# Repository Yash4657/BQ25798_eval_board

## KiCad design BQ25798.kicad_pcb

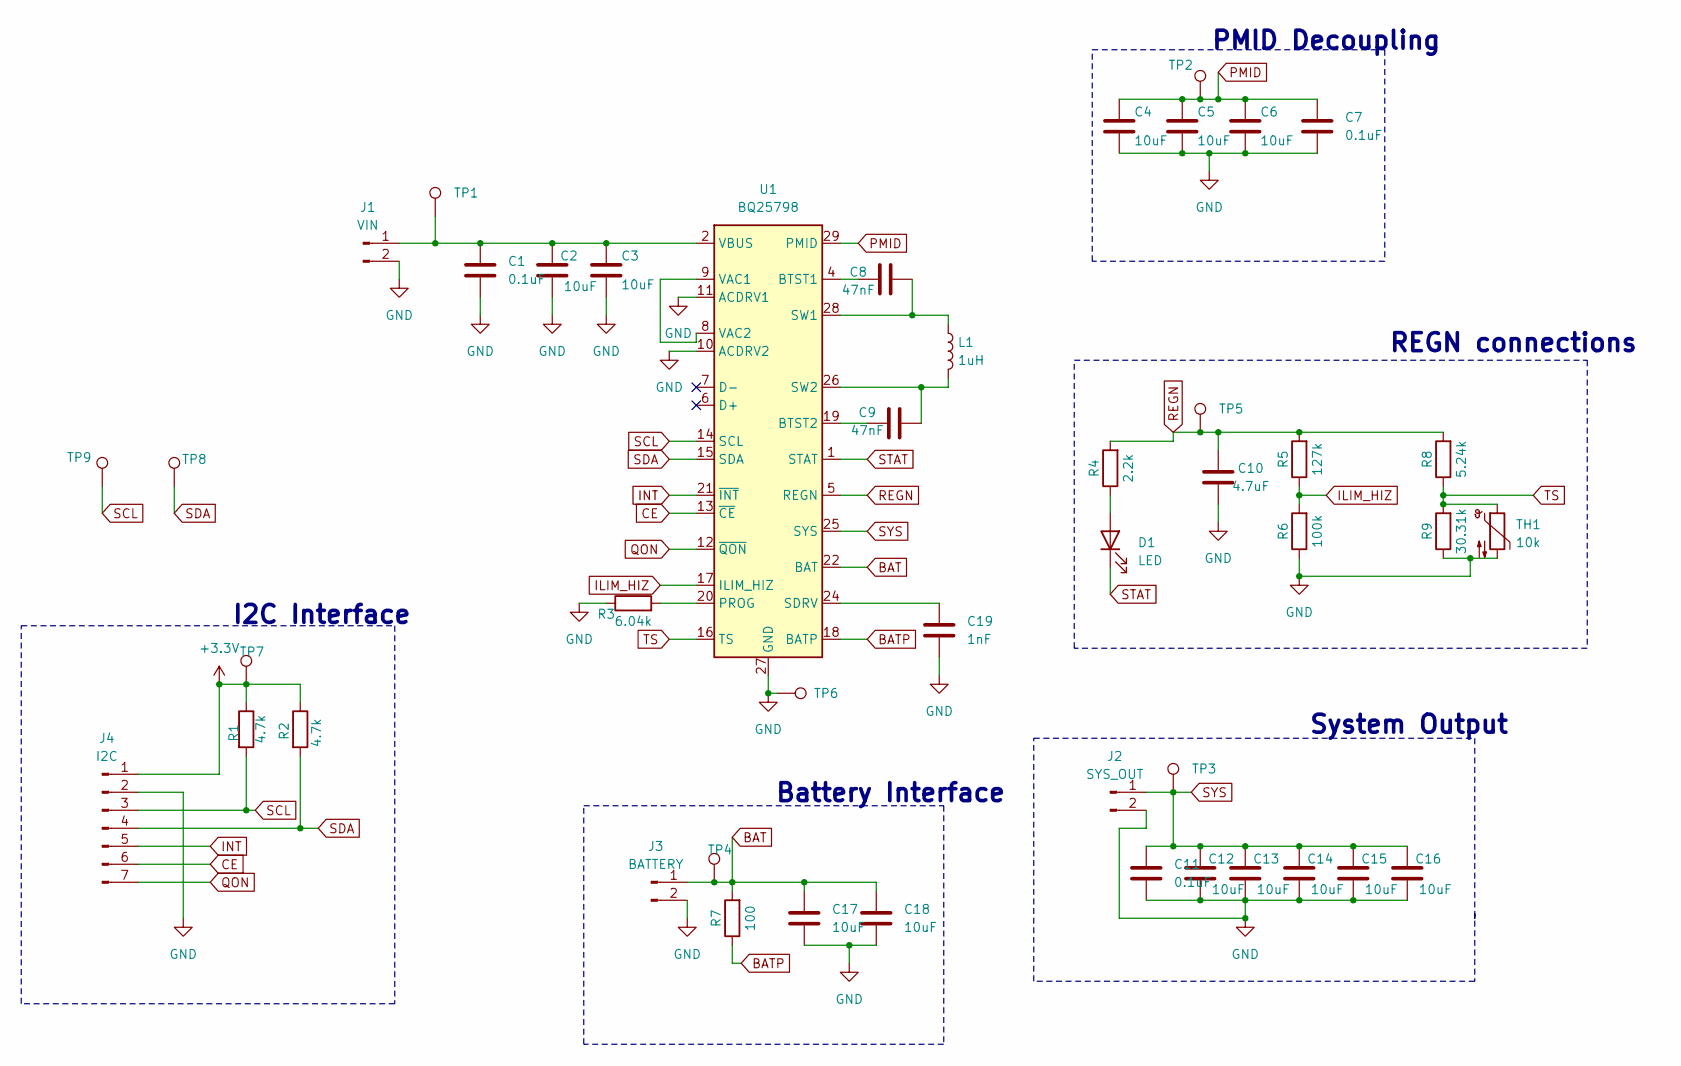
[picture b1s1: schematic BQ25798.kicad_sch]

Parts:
C1, C7, C11: 0.1uF; C_0805_2012Metric
C2, C3, C4, C5, C6, C12, C13, C14, C15, C16, C17, C18: 10uF; C_0805_2012Metric
C8, C9: 47nF; C_0805_2012Metric
C10: 4.7uF; C_0805_2012Metric
C19: 1nF; C_0805_2012Metric
D1: LED; LED_0805_2012Metric
J1: VIN; PinHeader_1x02_P2.54mm_Vertical
J2: SYS_OUT; PinHeader_1x02_P2.54mm_Vertical
J3: BATTERY; PinHeader_1x02_P2.54mm_Vertical
J4: I2C; PinHeader_1x07_P2.54mm_Vertical
L1: 1uH; IND_SPM6530T-1R0M120
R1, R2: 4.7k; R_0805_2012Metric
R3: 6.04k; R_0805_2012Metric
R4: 2.2k; R_0805_2012Metric
R5: 127k; R_0805_2012Metric
R6: 100k; R_0805_2012Metric
R7: 100; R_0805_2012Metric
R8: 5.24k; R_0805_2012Metric
R9: 30.31k; R_0805_2012Metric
TH1: 10k; R_0805_2012Metric
TP1, TP2, TP3, TP4, TP5, TP6, TP7, TP8, TP9: TestPoint_Pad_D1.5mm
U1: BQ25798; Texas_RQM0029A_VQFN-29_4x4mm_P0.4mm

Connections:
+3.3V: J4.1, R1.1, R2.1, TP7.1 (1_1)
BAT: C17.1, C18.1, J3.1, R7.2, TP4.1 (1_1), U1.22 (BAT), U1.23 (BAT)
BATP: R7.1, U1.18 (BATP)
CE: J4.6, U1.13 (~CE)
GND: C1.2, C2.2, C3.2, C4.2, C5.2, C6.2, C7.2, C10.2, C11.2, C12.2, C13.2, C14.2, C15.2, C16.2, C17.2, C18.2, C19.2, J1.2, J2.2, J3.2, J4.2, R3.1, R6.1, R9.1, TH1.2, TP6.1 (1_1), U1.10 (ACDRV2), U1.11 (ACDRV1), U1.27 (GND)
ILIM_HIZ: R5.1, R6.2, U1.17 (ILIM_HIZ)
INT: J4.5, U1.21 (~INT)
unnamed: D1.2 (A), R4.1
unnamed: C1.1, C2.1, C3.1, J1.1, TP1.1 (1_1), U1.2 (VBUS), U1.3 (VBUS)
unnamed: C8.1, U1.4 (BTST1)
unnamed: C9.1, U1.19 (BTST2)
unnamed: R3.2, U1.20 (PROG)
unnamed: C19.1, U1.24 (SDRV)
unnamed: C8.2, L1.1, U1.28 (SW1)
unnamed: C9.2, L1.2, U1.26 (SW2)
unnamed: U1.8 (VAC2), U1.9 (VAC1)
PMID: C4.1, C5.1, C6.1, C7.1, TP2.1 (1_1), U1.29 (PMID)
QON: J4.7, U1.12 (~QON)
REGN: C10.1, R4.2, R5.2, R8.2, TP5.1 (1_1), U1.5 (REGN)
SCL: J4.3, R1.2, TP9.1 (1_1), U1.14 (SCL)
SDA: J4.4, R2.2, TP8.1 (1_1), U1.15 (SDA)
STAT: D1.1 (K), U1.1 (STAT)
SYS: C11.1, C12.1, C13.1, C14.1, C15.1, C16.1, J2.1, TP3.1 (1_1), U1.25 (SYS)
TS: R8.1, R9.2, TH1.1, U1.16 (TS)

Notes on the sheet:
PMID Decoupling
REGN connections
I2C Interface
Battery Interface
System Output

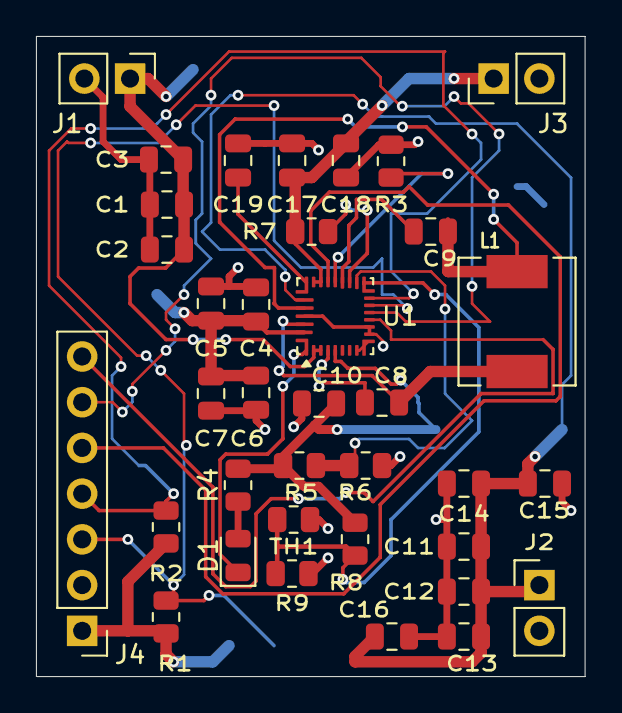
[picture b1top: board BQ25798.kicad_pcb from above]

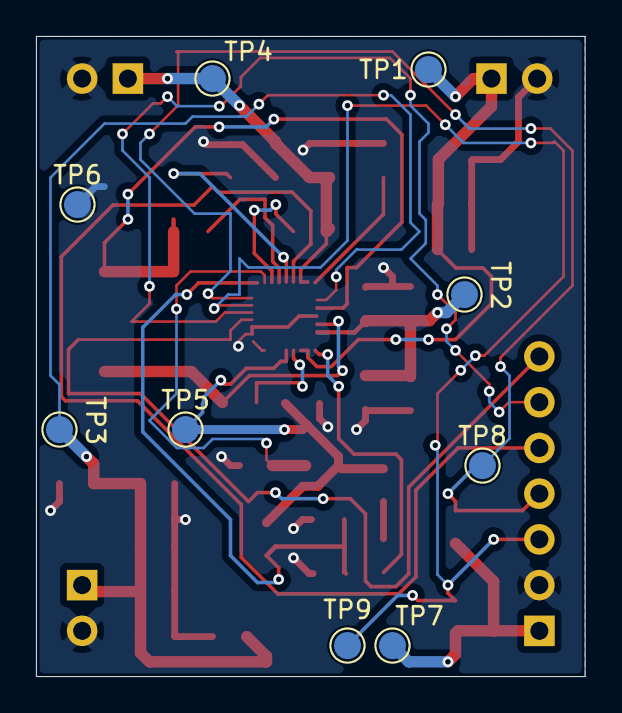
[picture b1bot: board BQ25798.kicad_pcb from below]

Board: 2 copper layers, 30.5 x 35.6 mm, 45 parts (9 on the bottom side), 24 nets.
